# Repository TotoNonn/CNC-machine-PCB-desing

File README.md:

# About project
I'm 700mV. I made this to try to help and to try to understand what happens in a cnc machine when you do all the parts. I started this project when I was in the university. The principal rason to do this is to do PCBs in house, for dont buy something than I can do it. The way is hard because I dont reach the same presition in a handmade machine that the presition in a really good machine made by a manufacturer or made whit super tools.
But is that the challenge, reach that.

## Objetive
Make a CNC machine whit my own tools, learn about everything that I can and help people like me.

Free tools for everyone.

-700mV

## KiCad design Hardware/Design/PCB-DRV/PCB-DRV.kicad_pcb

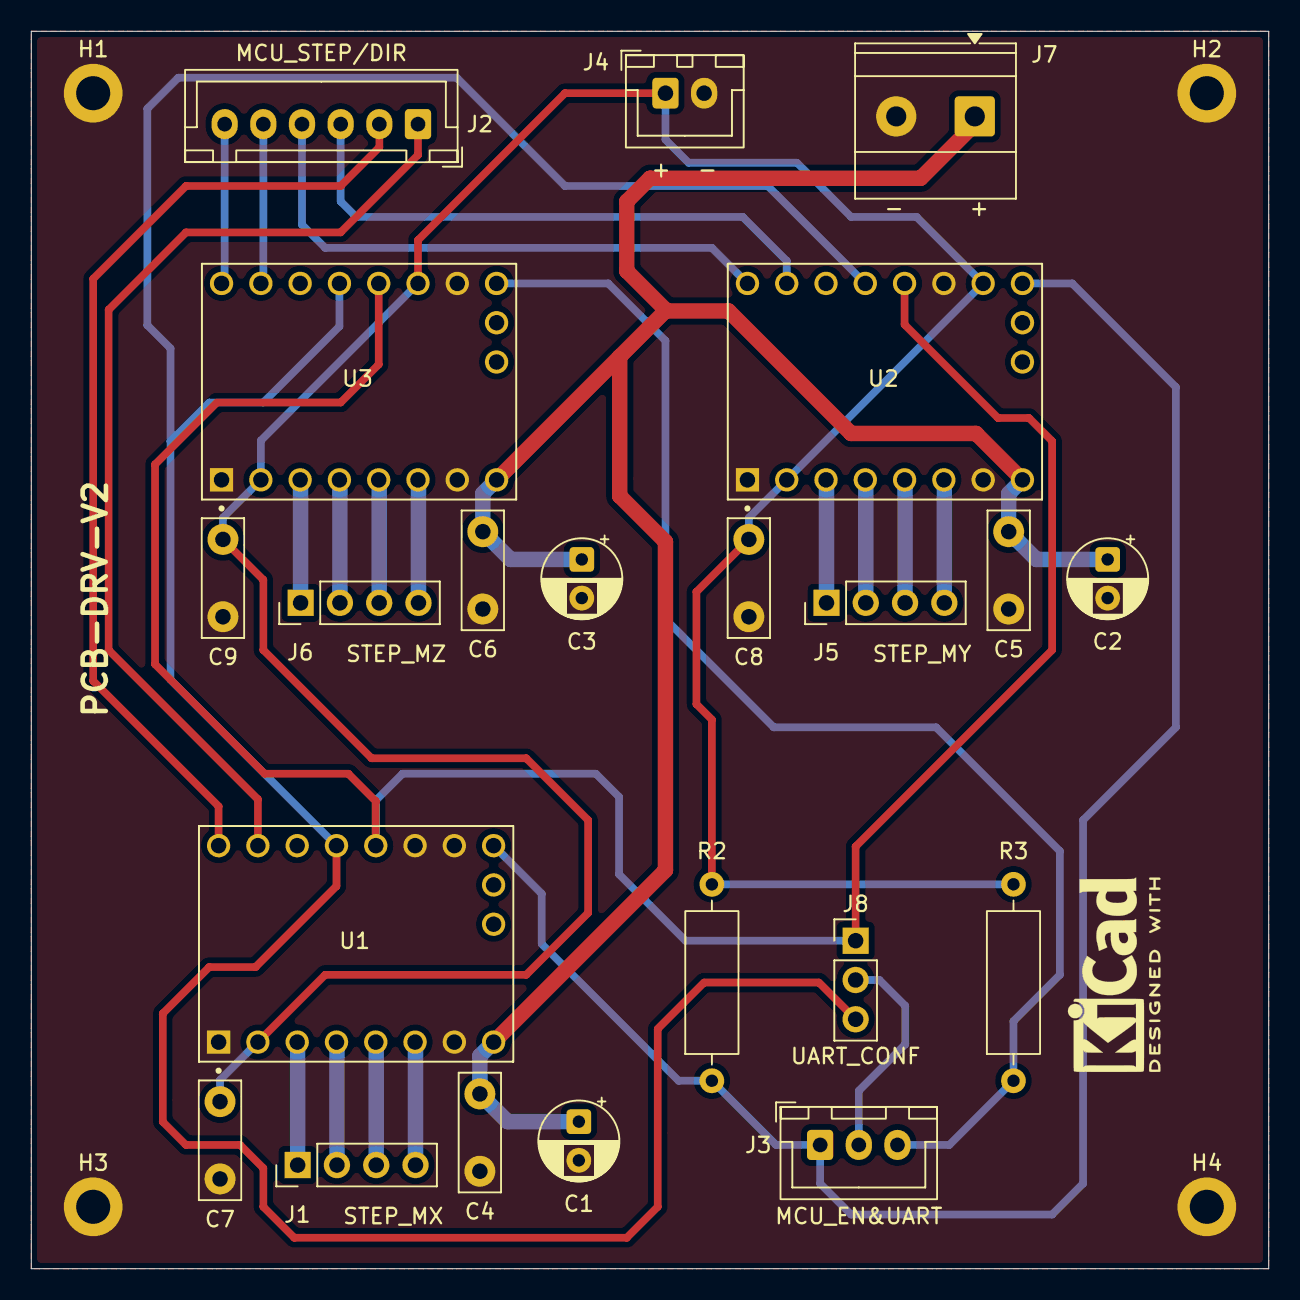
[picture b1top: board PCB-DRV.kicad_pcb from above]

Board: 2 copper layers, 80.0 x 80.0 mm, 26 parts (0 on the bottom side), 26 nets.

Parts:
C1, C2, C3: 100uF; CP_Radial_D5.0mm_P2.50mm
C4, C5, C6, C7, C8, C9: 100nF; C_Disc_D7.5mm_W2.5mm_P5.00mm
H1, H2, H3, H4: MountingHole_2.2mm_M2_DIN965_Pad
J1: STEP_MX; PinHeader_1x04_P2.54mm_Vertical
J2: MCU_STEP/DIR; JST_XH_B6B-XH-A_1x06_P2.50mm_Vertical
J3: MCU_EN&UART; JST_XH_B3B-XH-A_1x03_P2.50mm_Vertical
J4: +3.3V; JST_XH_B2B-XH-A_1x02_P2.50mm_Vertical
J5: STEP_MY; PinHeader_1x04_P2.54mm_Vertical
J6: STEP_MZ; PinHeader_1x04_P2.54mm_Vertical
J7: +12V; TerminalBlock_Phoenix_MKDS-1,5-2-5.08_1x02_P5.08mm_Horizont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
J8: UART_CONF; PinHeader_1x03_P2.54mm_Vertical
R2, R3: 10K; R_Axial_DIN0309_L9.0mm_D3.2mm_P12.70mm_Horizontal
U1, U2, U3: TMC2209_SILENTSTEPSTICK; MODULE_TMC2209_SILENTSTEPSTICK

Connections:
+3.3V: C7.1, C8.1, C9.1, J4.1, R2.2, R3.2, U1.2 (VIO), U2.2 (VIO), U2.15 (MS1), U3.2 (VIO), U3.14 (MS2)
+12V: C1.1, C2.1, C3.1, C4.1, C5.1, C6.1, J7.1, U1.8 (VM), U2.8 (VM), U3.8 (VM)
Ax1: J1.2, U1.4 (M1A)
Ax2: J1.1, U1.3 (M1B)
Ay1: J5.2, U2.4 (M1A)
Ay2: J5.1, U2.3 (M1B)
Az1: J6.2, U3.4 (M1A)
Az2: J6.1, U3.3 (M1B)
Bx1: J1.3, U1.5 (M2A)
Bx2: J1.4, U1.6 (M2B)
By1: J5.3, U2.5 (M2A)
By2: J5.4, U2.6 (M2B)
Bz1: J6.3, U3.5 (M2A)
Bz2: J6.4, U3.6 (M2B)
GND: C1.2, C2.2, C3.2, C4.2, C5.2, C6.2, C7.2, C8.2, C9.2, H1.1, H2.2, H3.3, H4.4, J4.2, J7.2, U1.1 (GND), U1.7 (GND), U1.14 (MS2), U1.15 (MS1), U2.1 (GND), U2.7 (GND), U2.14 (MS2), U3.1 (GND), U3.7 (GND), U3.15 (MS1)
GPIO_DIR_1: J2.2, U1.9 (DIR)
GPIO_DIR_2: J2.4, U2.9 (DIR)
GPIO_DIR_3: J2.6, U3.9 (DIR)
GPIO_EN_XY: J3.1, R2.1, U1.16 (~EN), U2.16 (~EN)
GPIO_EN_Z: J3.3, R3.1, U3.16 (~EN)
GPIO_STEP_1: J2.1, U1.10 (STEP)
GPIO_STEP_2: J2.3, U2.10 (STEP)
GPIO_STEP_3: J2.5, U3.10 (STEP)
GPIO_UART: J3.2, J8.2
GPIO_UART_SLNK: J8.3, U1.12 (UART), U2.12 (UART), U3.12 (UART)
GPIO_UART_V985: J8.1, U1.13 (SPRD), U2.13 (SPRD), U3.13 (SPRD)

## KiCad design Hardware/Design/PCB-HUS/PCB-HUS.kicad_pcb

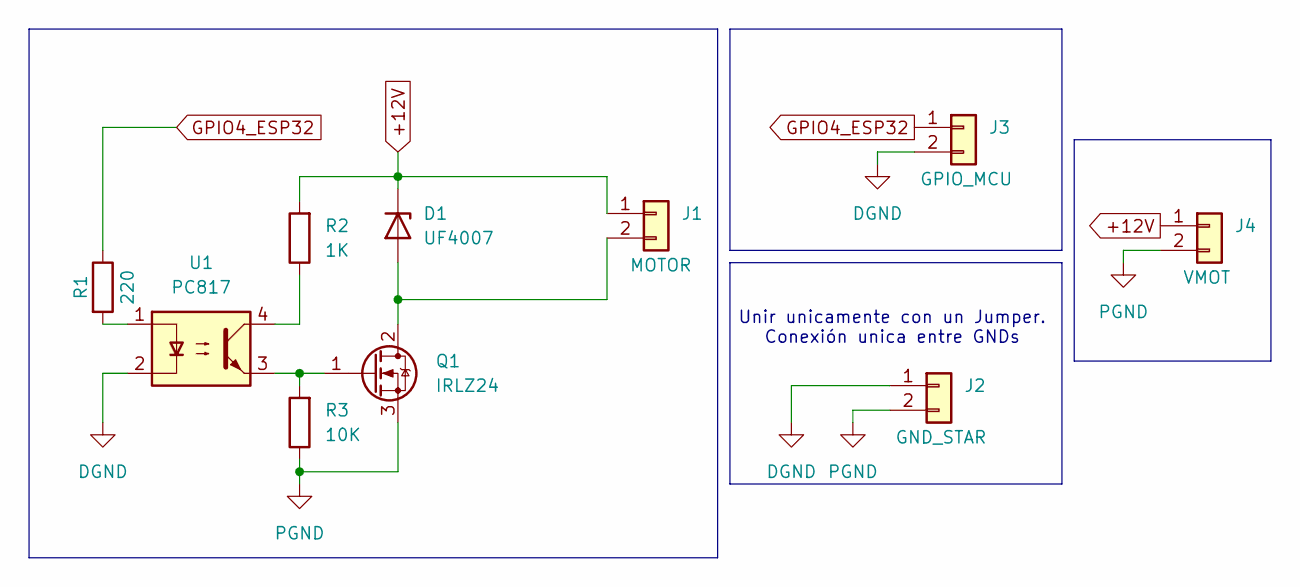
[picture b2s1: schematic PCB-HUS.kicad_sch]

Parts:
D1: UF4007; D_DO-41_SOD81_P10.16mm_Horizontal
J1: MOTOR; TerminalBlock_Phoenix_MKDS-1,5-2-5.08_1x02_P5.08mm_Horizont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
J2: GND_STAR; PinHeader_1x02_P2.54mm_Vertical
J3: GPIO_MCU; JST_XH_B2B-XH-A_1x02_P2.50mm_Vertical
J4: VMOT; TerminalBlock_Phoenix_MKDS-1,5-2-5.08_1x02_P5.08mm_Horizont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
Q1: IRLZ24; TO-220-3_Vertical
R1: 220; R_Axial_DIN0309_L9.0mm_D3.2mm_P12.70mm_Horizontal
R2: 1K; R_Axial_DIN0309_L9.0mm_D3.2mm_P12.70mm_Horizontal
R3: 10K; R_Axial_DIN0309_L9.0mm_D3.2mm_P12.70mm_Horizontal
U1: PC817; DIP-4_W7.62mm

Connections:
+12V: D1.1 (K), J1.1, J4.1, R2.2
DGND: J2.1, J3.2, U1.2
GPIO4_ESP32: J3.1, R1.1
unnamed: D1.2 (A), J1.2, Q1.2 (D)
unnamed: Q1.1 (G), R3.2, U1.3
unnamed: R1.2, U1.1
unnamed: R2.1, U1.4
PGND: J2.2, J4.2, Q1.3 (S), R3.1

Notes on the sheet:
Unir unicamente con un Jumper. Conexión unica entre GNDs

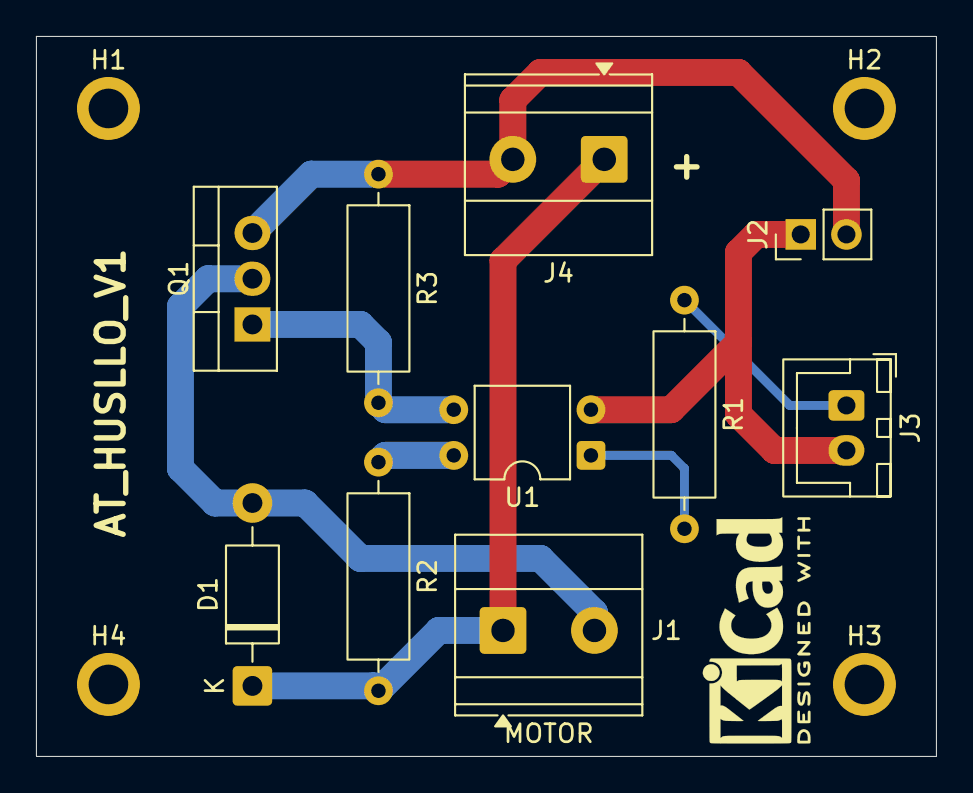
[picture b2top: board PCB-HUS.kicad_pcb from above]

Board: 2 copper layers, 50.0 x 40.0 mm, 14 parts (0 on the bottom side), 8 nets.

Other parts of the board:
H1, H2, H3, H4: MountingHole_2.2mm_M2_ISO7380_Pad

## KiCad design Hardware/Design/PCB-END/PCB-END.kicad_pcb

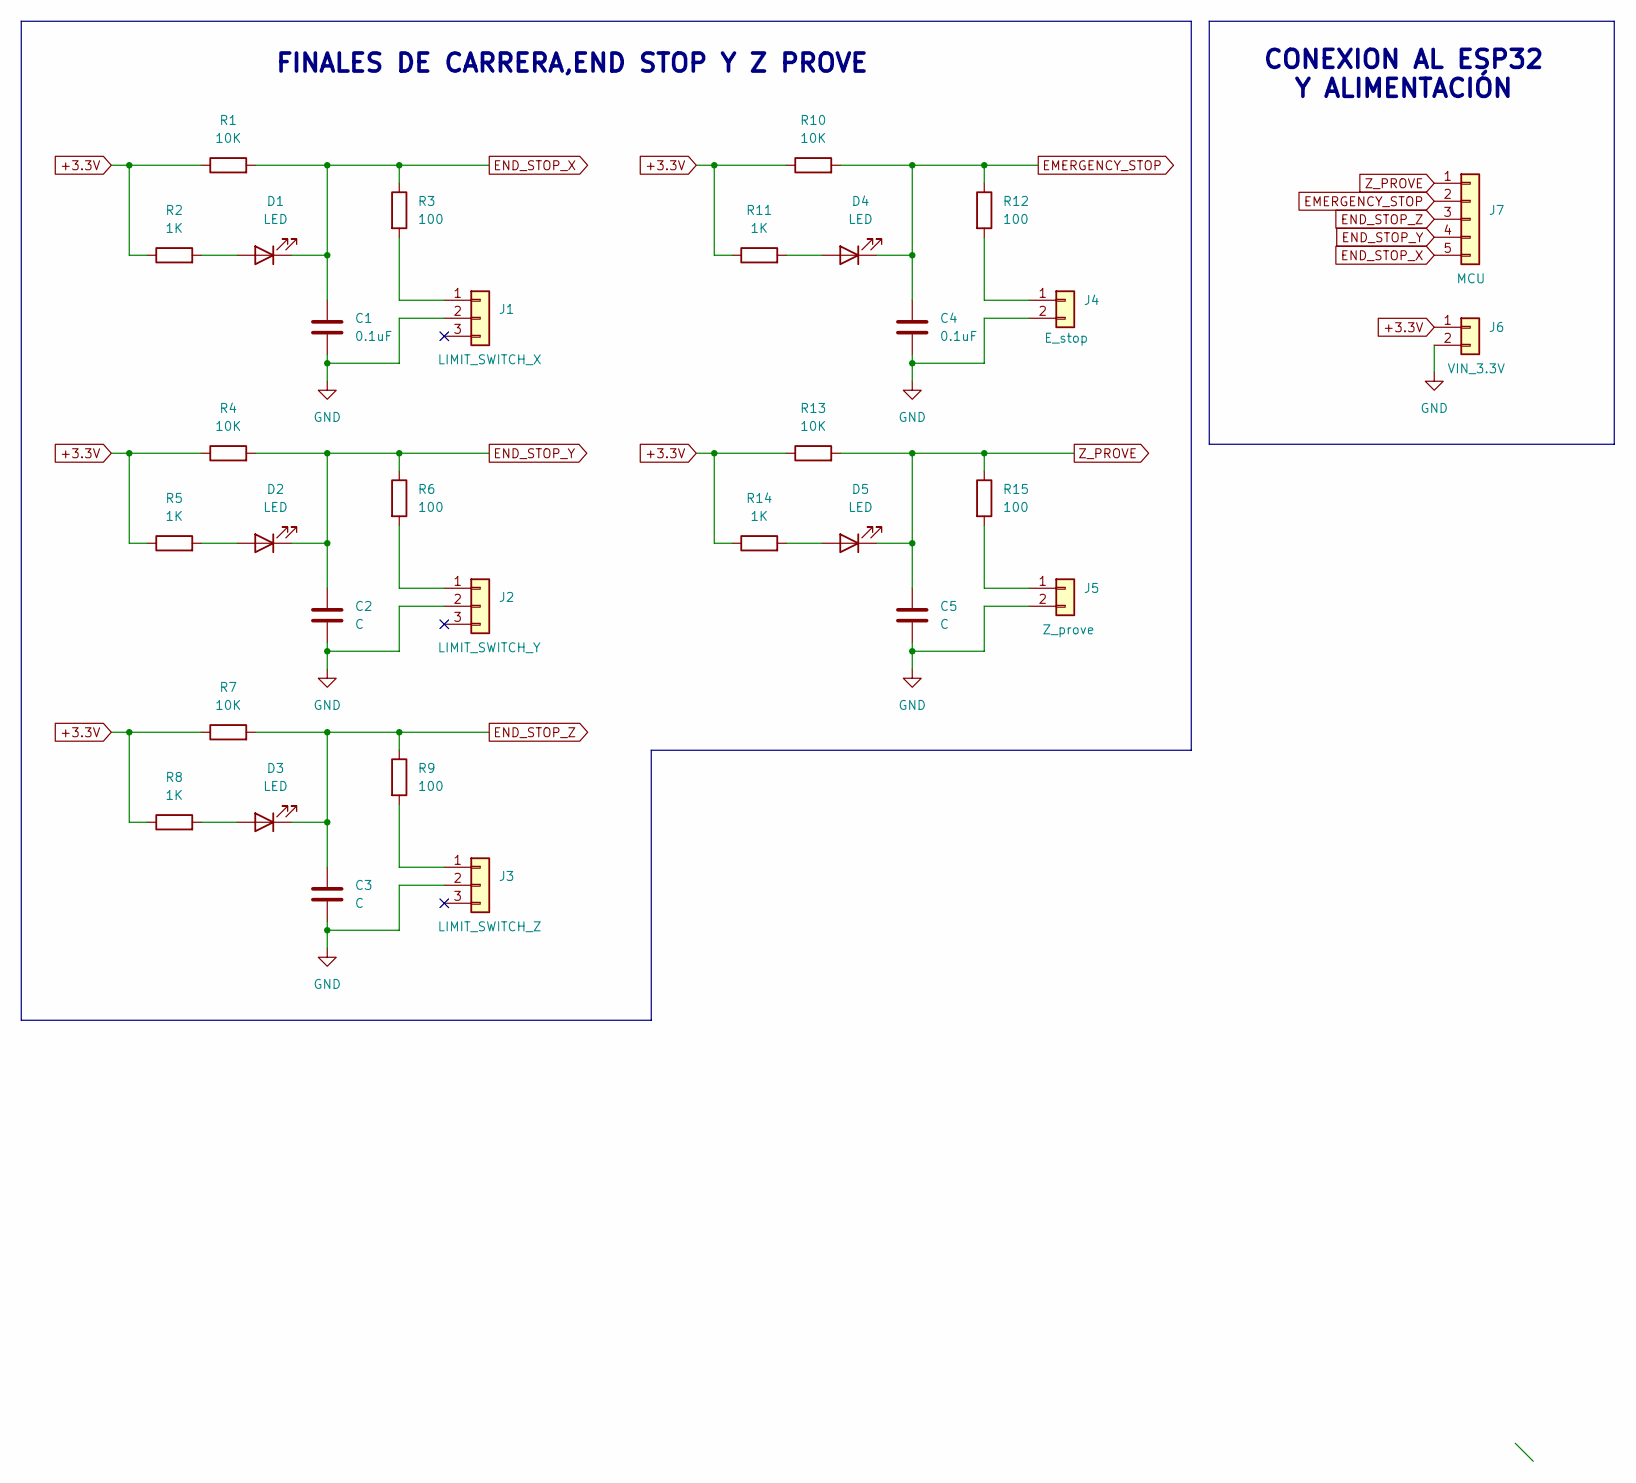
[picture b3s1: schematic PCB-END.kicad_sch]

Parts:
C1, C4: 0.1uF; C_Disc_D4.3mm_W1.9mm_P5.00mm
C2, C3, C5: C; C_Disc_D4.3mm_W1.9mm_P5.00mm
D1, D2, D3, D4, D5: LED; LED_D3.0mm
J1: LIMIT_SWITCH_X; JST_XH_B3B-XH-A_1x03_P2.50mm_Vertical
J2: LIMIT_SWITCH_Y; JST_XH_B3B-XH-A_1x03_P2.50mm_Vertical
J3: LIMIT_SWITCH_Z; JST_XH_B3B-XH-A_1x03_P2.50mm_Vertical
J4: E_stop; JST_XH_B2B-XH-A_1x02_P2.50mm_Vertical
J5: Z_prove; JST_XH_B2B-XH-A_1x02_P2.50mm_Vertical
J6: VIN_3.3V; JST_XH_B2B-XH-A_1x02_P2.50mm_Vertical
J7: MCU; JST_XH_B5B-XH-A_1x05_P2.50mm_Vertical
R1, R4, R7, R10, R13: 10K; R_Axial_DIN0309_L9.0mm_D3.2mm_P12.70mm_Horizontal
R2, R5, R8, R11, R14: 1K; R_Axial_DIN0309_L9.0mm_D3.2mm_P12.70mm_Horizontal
R3, R6, R9, R12, R15: 100; R_Axial_DIN0309_L9.0mm_D3.2mm_P12.70mm_Horizontal

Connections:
+3.3V: J6.1, R1.1, R2.1, R4.1, R5.1, R7.1, R8.1, R10.1, R11.1, R13.1, R14.1
EMERGENCY_STOP: C4.1, D4.1 (K), J7.2, R10.2, R12.1
END_STOP_X: C1.1, D1.1 (K), J7.5, R1.2, R3.1
END_STOP_Y: C2.1, D2.1 (K), J7.4, R4.2, R6.1
END_STOP_Z: C3.1, D3.1 (K), J7.3, R7.2, R9.1
GND: C1.2, C2.2, C3.2, C4.2, C5.2, J1.2, J2.2, J3.2, J4.2, J5.2, J6.2; also elsewhere on the board
unnamed: D1.2 (A), R2.2
unnamed: D2.2 (A), R5.2
unnamed: D3.2 (A), R8.2
unnamed: D4.2 (A), R11.2
unnamed: D5.2 (A), R14.2
unnamed: J1.1, R3.2
unnamed: J2.1, R6.2
unnamed: J3.1, R9.2
unnamed: J4.1, R12.2
unnamed: J5.1, R15.2
Z_PROVE: C5.1, D5.1 (K), J7.1, R13.2, R15.1

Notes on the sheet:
CONEXION AL ESP32 Y ALIMENTACIÓN
FINALES DE CARRERA,END STOP Y Z PROVE

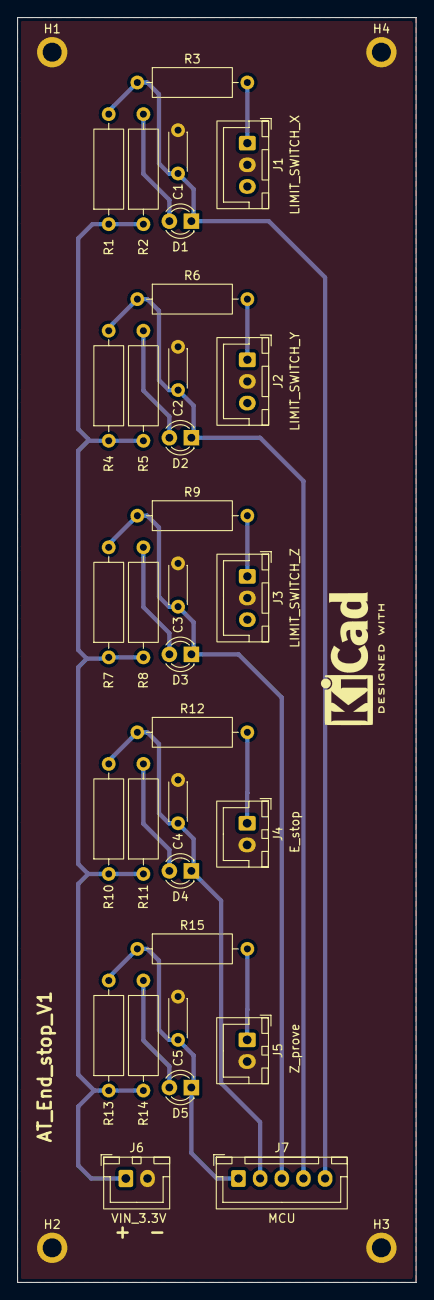
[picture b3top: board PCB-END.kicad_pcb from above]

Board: 2 copper layers, 46.0 x 146.0 mm, 36 parts (0 on the bottom side), 17 nets.

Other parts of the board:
H1, H2, H3, H4: MountingHole_2.2mm_M2_ISO7380_Pad

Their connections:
GND: H1.1, H2.2, H3.3, H4.4; also elsewhere on the board

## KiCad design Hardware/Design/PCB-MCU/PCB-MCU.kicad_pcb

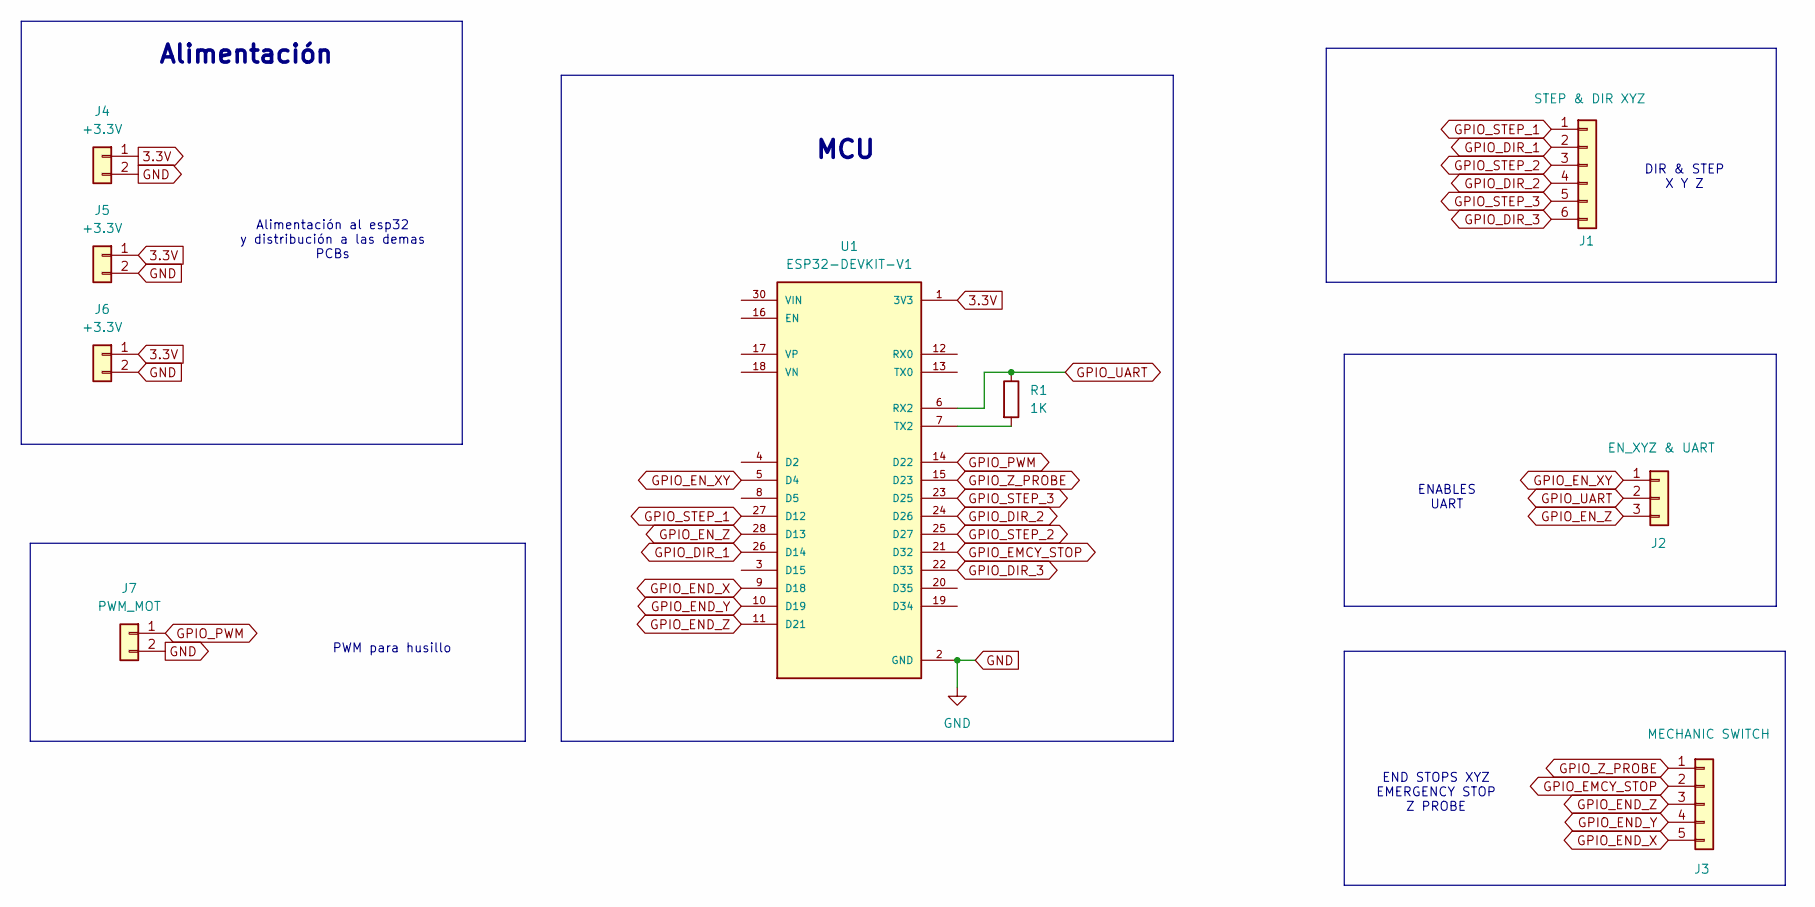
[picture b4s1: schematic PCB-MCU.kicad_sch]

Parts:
J1: STEP & DIR XYZ; JST_XH_B6B-XH-A_1x06_P2.50mm_Vertical
J2: EN_XYZ & UART; JST_XH_B3B-XH-A_1x03_P2.50mm_Vertical
J3: MECHANIC SWITCH; JST_XH_B5B-XH-A_1x05_P2.50mm_Vertical
J4, J5, J6: +3.3V; JST_XH_B2B-XH-A_1x02_P2.50mm_Vertical
J7: PWM_MOT; JST_XH_B2B-XH-A_1x02_P2.50mm_Vertical
R1: 1K; R_Axial_DIN0207_L6.3mm_D2.5mm_P7.62mm_Horizontal
U1: ESP32-DEVKIT-V1; MODULE_ESP32_DEVKIT_V1; PARTREV N/A

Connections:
3.3V: J4.1, J5.1, J6.1, U1.1 (3V3)
GND: J4.2, J5.2, J6.2, J7.2, U1.2 (GND), U1.29 (GND)
GPIO_DIR_1: J1.2, U1.26 (D14)
GPIO_DIR_2: J1.4, U1.24 (D26)
GPIO_DIR_3: J1.6, U1.22 (D33)
GPIO_EMCY_STOP: J3.2, U1.21 (D32)
GPIO_END_X: J3.5, U1.9 (D18)
GPIO_END_Y: J3.4, U1.10 (D19)
GPIO_END_Z: J3.3, U1.11 (D21)
GPIO_EN_XY: J2.1, U1.5 (D4)
GPIO_EN_Z: J2.3, U1.28 (D13)
GPIO_PWM: J7.1, U1.14 (D22)
GPIO_STEP_1: J1.1, U1.27 (D12)
GPIO_STEP_2: J1.3, U1.25 (D27)
GPIO_STEP_3: J1.5, U1.23 (D25)
GPIO_UART: J2.2, R1.1, U1.6 (RX2)
GPIO_Z_PROBE: J3.1, U1.15 (D23)
unnamed: R1.2, U1.7 (TX2)

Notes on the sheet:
MCU
Alimentación
ENABLES UART
DIR & STEP X Y Z
Alimentación al esp32 y distribución a las demas PCBs
END STOPS XYZ EMERGENCY STOP Z PROBE
PWM para husillo

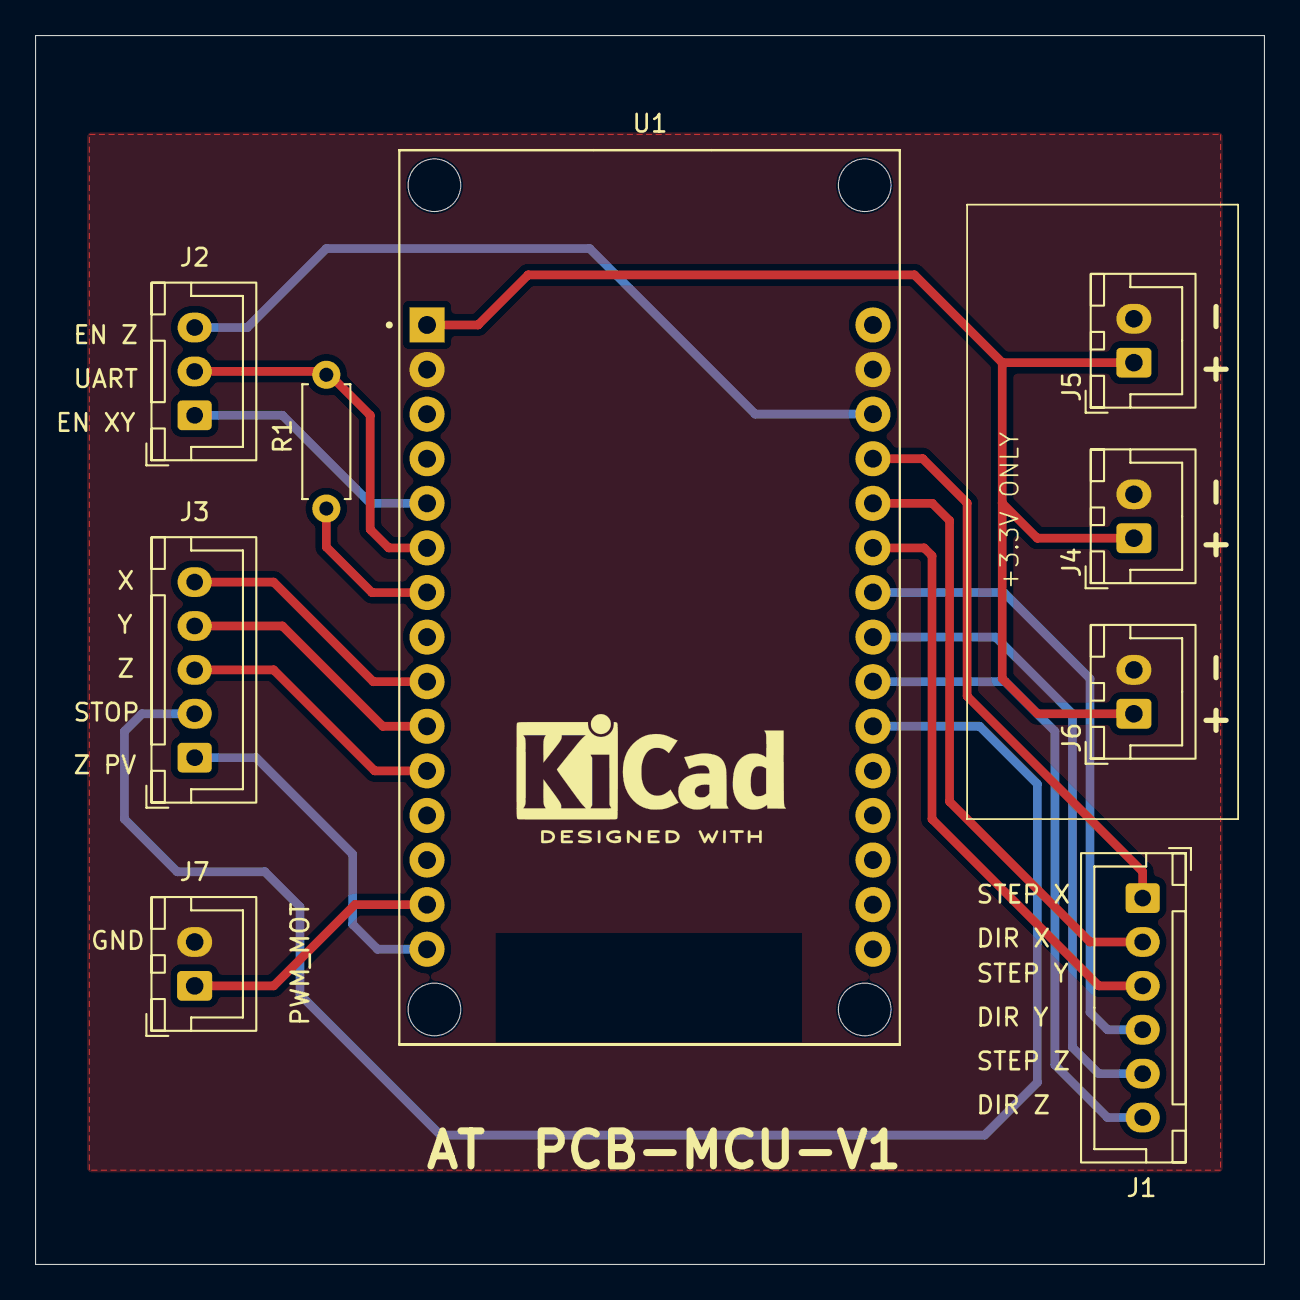
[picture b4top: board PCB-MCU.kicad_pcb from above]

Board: 2 copper layers, 70.0 x 70.0 mm, 9 parts (0 on the bottom side), 18 nets.
